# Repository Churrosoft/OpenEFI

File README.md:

# OpenEFI: 

OpenEFI es un sistema de inyección OpenSource configurable y adaptable a casi cualquier vehiculo con motores a Nafta/Gasohol/GNC/GLP

Está planeado el soporte a corto y largo plazo para:
-   Motores a nafta con inyección y encendido electrónico
-  calculo de tiempo de inyección a partir de tablas pre-definidas | Alpha Plus | Speed Density
-  Soporte de inyectores de alta impedancia (los de baja más adelante por requerir PWM además del tiempo de inyeccion)
-   Soporte para GNC/GLP con tablas independientes
-   Motores diesel con inyección directa
-   Motores de 1 a 8 cilindros

## Sobre el Software
la plataforma se ejecuta desde un STM32F103, conocido como "bluepill", para facilitar la programación del mismo, se utiliza el bootloader: [dapboot](https://github.com/devanlai/dapboot)

### Como generar los binarios:
se necesitan las siguientes herramientas:

    GNU Arm Embedded Toolchain
    sudo dnf install gcc systemd-devel ncurses-devel ncurses-compat-libs
    rustup override set nightly
    rustup target add thumbv7em-none-eabihf
    rustup component add llvm-tools-preview arm-none-eabi-newlib
    cargo install cargo-binutils cargo-embed cargo-flash cargo-expand

pasos para grabar el firmware:

 1. Compile y grabe el bootloader => [dapboot](https://github.com/devanlai/dapboot)
 2. clone el repositorio con git o descarguelo
 3. dentro del repo ejecutar: `make flash-usb`

## Sobre el Hardware

### Preguntas frecuentes:
### ¿hay algún video sobre el funcionamiento de la ECU / EFI ?
No, por el momento solo tenemos avances en el diseño de los pcb's, pero todavía el hardware ni el software se encuentra preparado para una prueba real en un motor, estimamos nuestro primer test a finales del 2020 si es que no nos morimos antes
### ¿cómo hacen para adaptar el hardware a una configuración tan amplia?
Porque el tratamiento de las señales analógicas para la mayoría de los sensores son iguales, consta de un filtro paso bajo y un diodo para evitar el sobre voltaje, se intentan mantener simples para que sea fácil de mantener, luego se aplican otros filtros en software para mejorar aún más esto

### ¿se pueden revisar los esquemas en algún lado, y obtener más información en general de la placa?
Claro!, todo lo referido al hardware se encuentra en [OpenEFI-PCB](https://github.com/openefi/OpenEFI-PCB)

## Sobre la configuracion

### Preguntas frecuentes:
### ¿como se va a configurar todo esto?
para la configuracion inicial, y para la visualizacion de parametros en tiempo real, se utiliza [OpenEFI-Tuner](https://github.com/openefi/OpenEFI-Tuner) , la idea es que tengas unicamente que conectar la EFI a tu computadora, entrar a [tuner.openefi.xyz](http://tuner.openefi.xyz/) y empezar a jugar, sin tener que pasar por la tortura de instalar drivers, programas,etc , aunque tambien puedes montar tu propio OpenEFI-Tuner en tu servidor local si quieres !, aunque la aplicación web funcionara sin conexión a internet

### ¿tiene soporte para un scanner común?¿cómo se leen los DTC's?
No, por el momento no tenemos planeado agregar soporte a CAN hasta llegar al MVP, así que no se pueden usar scanners automotrices normales acá
para leer los DTC se utiliza OpenEFI-Tuner

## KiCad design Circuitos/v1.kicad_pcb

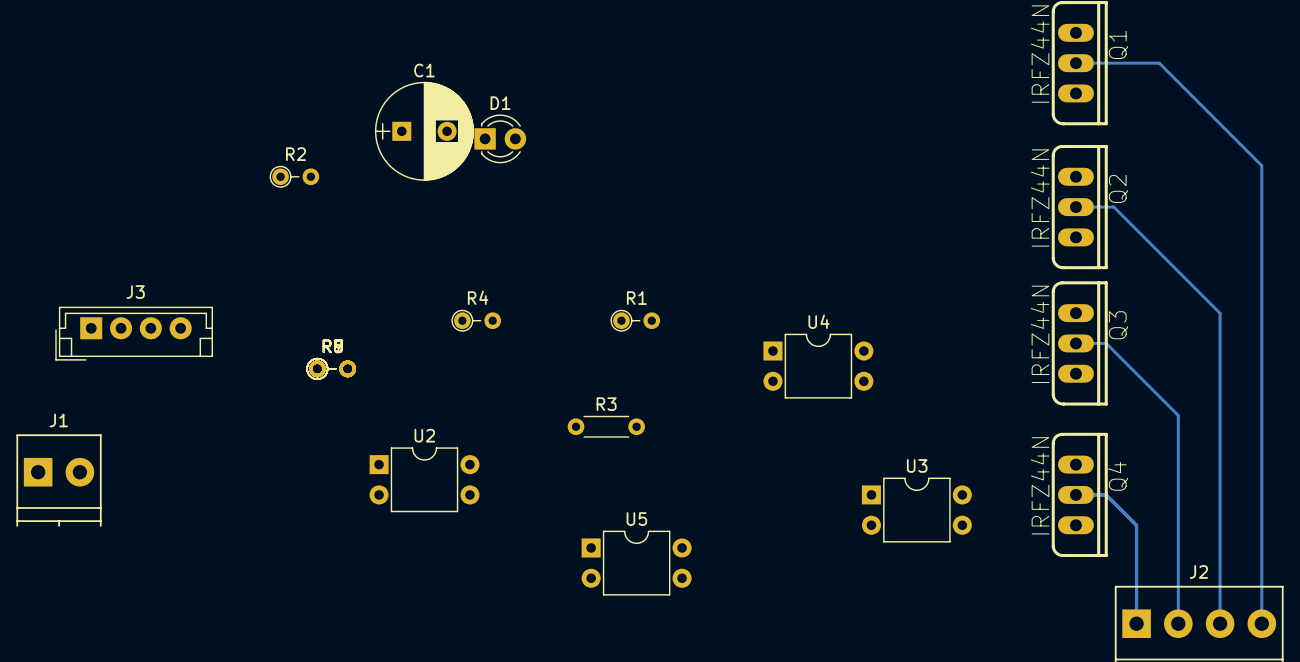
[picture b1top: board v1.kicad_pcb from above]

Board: 2 copper layers, 22 parts (0 on the bottom side), 19 nets.

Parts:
C1: 500u; CP_Radial_D8.0mm_P3.80mm
D1: LED; LED_D3.0mm_FlatTop
J1: 12v; TerminalBlock_Pheonix_PT-3.5mm_2pol
J2: Inyectores; TerminalBlock_Pheonix_PT-3.5mm_4pol
J3: CONN_01X04; JST_EH_B04B-EH-A_04x2.50mm_Straight
Q1, Q2, Q3, Q4: IRFZ44N; TO-220
R1: 1.2k; R_Axial_DIN0204_L3.6mm_D1.6mm_P2.54mm_Vertical
R2: 220r; R_Axial_DIN0204_L3.6mm_D1.6mm_P2.54mm_Vertical
R3: 4.7k; R_Axial_DIN0204_L3.6mm_D1.6mm_P5.08mm_Horizontal
R4, R6, R8: 220; R_Axial_DIN0204_L3.6mm_D1.6mm_P2.54mm_Vertical
R5: 4.7K; R_Axial_DIN0204_L3.6mm_D1.6mm_P2.54mm_Vertical
R7, R9: 4.7k; R_Axial_DIN0204_L3.6mm_D1.6mm_P2.54mm_Vertical
U2, U3, U4, U5: PC817; DIP-4_W7.62mm

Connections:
+12V: C1.1, J1.1, R1.1, R3.1, R5.1, R7.1, R9.1
Earth: C1.2, D1.1, J1.2, Q1.3, Q2.3, Q3.3, Q4.3, U2.2, U2.3, U3.2, U3.3, U4.2, U4.3, U5.2, U5.3
unnamed: D1.2, R1.2
unnamed: J2.1, Q4.2
unnamed: J2.2, Q3.2
unnamed: J2.3, Q2.2
unnamed: J2.4, Q1.2
unnamed: J3.1, R8.1
unnamed: J3.2, R6.1
unnamed: J3.3, R4.1
unnamed: J3.4, R2.2
unnamed: Q1.1, R3.2, U2.4
unnamed: Q2.1, R5.2, U3.4
unnamed: Q4.1, R9.2, U5.4
unnamed: R2.1, U2.1
unnamed: R4.2, U3.1
unnamed: R6.2, U4.1
unnamed: R7.2, U4.4
unnamed: R8.2, U5.1

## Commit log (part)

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2021-07-01 fix on launch_qemu script
2021-07-01 fix on core dump
2021-07-02 Create CNAME
2021-07-09 update on cpwm tests
2021-07-09 Deploy code docs to GitHub Pages build: 1016453644
    Commit: f49efb4e9a3f0d3858e90e6aa982c0b1a4395ed4
2021-07-12 added CPWM TIM3/4 stops
2021-08-03 FEAT: added tables namespace & basic operations
2021-08-23 Update on memory lib, now working simple I/O and DTC
2021-08-23 Updated deeps
2021-08-23 Deploy code docs to GitHub Pages build: 1157413025
    Commit: 3b184d702fc557cabea5c282cefa0d1845dd5d56
2021-08-23 Deploy code docs to GitHub Pages build: 1157451508
    Commit: c42740731e1a668fef26d181cf277c648f3431ef
2021-09-13 Deploy code docs to GitHub Pages build: 1231494850
    Commit: 5bd9b98b9723b0efd94b7c8af0e83e4001a633d5
2021-09-17 Deploy code docs to GitHub Pages build: 1244193873
    Commit: 0fabc0332efac8498607876999c042d3038082ba
2021-10-22 added ignition skeleton
2021-10-31 init pmic lib
2021-10-31 init webusb/control_interface code
2021-11-01 init webusb
2021-11-01 fix on process_frame / usb_cdc_if
2021-11-02 init tinyusb, not working
2021-11-02 full assert, change all char on cdc messages to uint8_t
2021-11-02 Deploy code docs to GitHub Pages build: 1413399338
    Commit: 7a87897e626b4160cce1ea6a59e9883043316fda
2021-11-04 added basic DTC check && common functions
2021-11-06 WIP: pmic dtc
2021-11-07 clean dtc functions
2021-11-07 added logs for injection/ignition registers
2021-11-09 minor fix on pmic
2021-11-09 SPI Working, 16Mhz clock, APB 8Mhz/16Mhz
2021-11-09 Deploy code docs to GitHub Pages build: 1441497642
    Commit: 279cf7ebe5776f444bb770d32a6d8fef5648664f
2021-11-10 32Mhz, 32-32 APB1
2021-11-15 wip: new memory lib
2021-11-18 clean main.cpp
2021-11-19 update deeps
2021-11-19 removed unused git dep
2021-11-19 bypass git commit erros on docs workflow
2021-11-20 Deploy code docs to GitHub Pages build: 1485550335
    Commit: 67af5ce9863826d8c5fd4a6f194a30d7fbc0cddf
2021-11-20 Deploy code docs to GitHub Pages build: 1485556337
    Commit: 969b88aafd36334eed82a1901a42424d64db6494
2021-11-20 Deploy code docs to GitHub Pages build: 1485568736
    Commit: df8b38b50a30b3eb1ae8ba0f820c8099bec0384a
2021-11-21 update on tables docs
2021-11-21 add tables to "Tables" module on doxygen
2021-11-21 fix addtogroup
2021-11-21 Deploy code docs to GitHub Pages build: 1486188713
    Commit: f7c0086929e30eba8c77736e418d7ed388bab34b
2021-11-27 Deploy code docs to GitHub Pages build: 1509794399
    Commit: 9b121dbe67fb439603781c0cc1f22537bcc6d86a
2021-12-03 Deploy code docs to GitHub Pages build: 1533751412
    Commit: b9104ecd271a490c1d45c628d70236e9f9446ee5
2021-12-24 Deploy code docs to GitHub Pages build: 1619996899
    Commit: 0f366000278b73afb32a38d6aa9cce0f127bae32
2021-12-24 Deploy code docs to GitHub Pages build: 1620003454
    Commit: e1af8d8e8f584061cc870fb3b91b4f4d0517b61b
2021-12-27 remove old usb files
2021-12-29 added webserial handler
2021-12-30 feat/webusb-tables, added basic table logic
2021-12-30 FEAT: WebSerial, read table from memory
2021-12-31 Deploy code docs to GitHub Pages build: 1639424144
    Commit: 4b64be70c5e0852dc5f9383cf8269caf9ffa4906
2022-01-04 Deploy code docs to GitHub Pages build: 1655948204
    Commit: 34130f2e801d7fce79e043f53d357108d9ee9b5f
2022-01-15 Deploy code docs to GitHub Pages build: 1700718618
    Commit: 53558dbc50a4f2d84345c06d540178410e54df73
2022-01-19 Deploy code docs to GitHub Pages build: 1716340558
    Commit: ee223321686fe4155cdb6493309cade1581cdb9e
2022-01-20 Deploy code docs to GitHub Pages build: 1720895698
    Commit: b3412914407d7c9e457cb63f76f27e256bfa9b82
2022-01-20 Deploy code docs to GitHub Pages build: 1721854263
    Commit: 43b6b9a9222052b53d707c965d56cabb615f6cdd
2022-01-23 Deploy code docs to GitHub Pages build: 1734966643
    Commit: 3ef56f0a33d6755fc373801c92773fc52597df15
2022-01-23 Deploy code docs to GitHub Pages build: 1735087944
    Commit: 9d922380e224e2591fbe0111e45802dc02b3d6a9
2022-01-24 Deploy code docs to GitHub Pages build: 1737586589
    Commit: 47d716514ab19abfa86c4fc6f8744ed08c57e846
2022-01-24 Deploy code docs to GitHub Pages build: 1742554132
    Commit: 755486aae8f00284daafb2e0aa637a1fab09f438
2022-01-24 bump sensors datasize from u16b to 32b
2022-01-25 fix webusb command crash
2022-01-31 fix MAP sensor *ponele*
2022-02-01 fix MAP::get_value
2022-02-03 Deploy code docs to GitHub Pages build: 1787734713
    Commit: 579d0b852aaadf1c419077d256d7fc0e3230d904
2022-02-05 Deploy code docs to GitHub Pages build: 1798473722
    Commit: da29d176e9ef3d0c08db56140d16a8405699ffbe
2022-02-20 updated sensors to MCP3208 adc, "it just works!"
2022-02-23 Deploy code docs to GitHub Pages build: 1885192609
    Commit: a0203b4a40d93ea7121798f93fac7c1cbd6f49df
2022-03-15 Deploy code docs to GitHub Pages build: 1989814801
    Commit: 51ca8f853e378f431f841141d17d8268b1103741
2022-03-29 Deploy code docs to GitHub Pages build: 2061678119
    Commit: 49189d71a0523734020142ddc3f9d7886315b779
2022-03-31 Deploy code docs to GitHub Pages build: 2073986722
    Commit: 3233be1ace1a9ae52a400febe78c226a04d7c764
2022-04-04 Deploy code docs to GitHub Pages build: 2087326653
    Commit: 0f93b00aa9f5c8ca35611cf387d53db2153d8b27
2022-04-11 new rpm calc
2022-04-12 updated tim1 source, added tim11 for rpm
2022-04-13 update HAL_TIM_PeriodElapsedCallback
2022-04-20 update hal internals
2022-04-28 bump core to uefi rev3
2022-04-28 remove adc
2022-05-07 wip v3
2022-05-12 updated core
2022-05-12 Deploy code docs to GitHub Pages build: 2311276295
    Commit: a6de2b014bd950bc46fe00f7edc9891d851b5039
2022-05-14 fix rpmdiff if
2022-05-16 cpwm: fix rpm calculation
2022-05-23 update C_PWM defines
2022-05-29 fix mockRPM
2022-05-29 added rpm status
2022-06-23 update webusb command definition
2022-06-28 "Funca o segfault", enviar trace por webserial
2022-06-30 fix webserial deque
2022-06-30 fix efi_invert_pin
2022-06-30 fix junit report message generation
2022-06-30 Deploy code docs to GitHub Pages build: 2592961736
    Commit: 1c75aba06defbba6776105cc38ca4eacd13c50e0
2022-07-01 CAN Wrapper headers
2022-07-06 add obd pid/status
2022-07-07 update NVIC priority
2022-07-29 add RPM::watch_dog
2022-08-17 can/obd wrapper init
2022-08-19 add can rx logic
2022-08-26 pa que recarajo pones el swap si luego vas a asignarlo como puntero lrpm
2022-08-27 fix OBD2 REQUEST_AVAILABLE_SID
2022-08-30 los swap ameooo, add CF logic to TX code
2022-09-05 Deploy code docs to GitHub Pages build: 2990528308
    Commit: 80d9df85cb7a8d346e4033e6bc3eaa170ef2f689
2022-09-06 Deploy code docs to GitHub Pages build: 2997390508
    Commit: b1b04253f7411039b74acb19d388a9bf06b12a13
2022-09-06 Deploy code docs to GitHub Pages build: 2997430793
    Commit: f43355f2547e79776dd6e6161ff541aad6274a79
2022-09-13 Deploy code docs to GitHub Pages build: 3042237243
    Commit: e7b73391949561e59798c9ae1bc705e1ac280b73
2022-09-13 Deploy code docs to GitHub Pages build: 3042253908
    Commit: f23cb249f4f15cab6e6a3582a7675c296464c21a
2022-09-16 Deploy code docs to GitHub Pages build: 3064888050
    Commit: f97e93bec8afc55a67206df36248d87ea51440e7
2022-09-27 Create LICENSE
2022-10-01 add .venv to gitignore
2022-10-04 fix sensors build
2022-10-06 Deploy code docs to GitHub Pages build: 3194318525
    Commit: db250aa3ef30542540a1e8f96d7bd9a610fb27f7
2022-10-06 Feature WebSerial: Add sensors/ignition/injection to core_status
2022-10-13 Deploy code docs to GitHub Pages build: 3245793454
    Commit: af0a6e2f804cc41290d5549539740356056c3188
2022-10-18 fix crc calculation, fix table read/write with offset
2022-10-19 update sensors lib
2022-10-21 Add CRC32 check on table write from Tuner (only full data, individual row wip)
2022-10-22 add mocks on webusb
2022-11-27 doxygen memory/tables
2022-12-03 wip injection, alpha N
2022-12-03 Deploy code docs to GitHub Pages build: 3610153926
    Commit: 2de543c3618dfd6996af6f8ea946c04486382581
2022-12-08 Deploy code docs to GitHub Pages build: 3644989836
    Commit: 0f0e014570b0edeb57b3a2ec89f83f73a9dbadf0
2022-12-13 WIP: injection timming, air model based on alphaN
2022-12-16 WIP: platformio testing
2022-12-20 wip alphaN tests
2022-12-22 fix lambda values, fix alphaN air calculation
2022-12-25 new config struct with memory backup
2022-12-26 fix efi_cfg
2022-12-31 fix table ram update
2023-01-08 add json lib
2023-01-08 fix firmware test build
2023-01-10 Deploy code docs to GitHub Pages build: 3886154374
    Commit: 34fbefca446bb27125b7482cc9a9118c8aa05cd1
2023-02-04 bootloader fix
2023-02-05 Ignore dirty w25qxx submodule
2023-02-05 Bootloader integration
2023-02-05 Deploy code docs to GitHub Pages build: 4098374462
    Commit: 687b344cd22707f27602d007917e0bf0b307f107
2023-02-05 Deploy code docs to GitHub Pages build: 4098441500
    Commit: 02182db54ea026f7fdd7927fdb9698a09ef84702
2023-02-09 add upload script
2023-02-09 wip core:gpio config
2023-02-09 Change target to thumbv7em-none-eabihf
2023-02-09 Add gdbinit for debugging within clion
2023-02-10 Improving debugging with clion
2023-02-10 wip gpio
2023-02-11 oneshot test
2023-02-11 soy un tarado.rs
2023-02-12 Move all modules into the app module.
2023-02-12 ckp trigger interrupt
2023-02-12 Sending CDC replies via task
2023-02-12 Log timestamps
2023-02-15 memory table read, wip validate from crc
2023-02-17 wip, fix memory erase
2023-02-24 fixes on calculate_injection_fuel
2023-02-27 fix gdb, wip json config
2023-03-12 wip: add cpwm && rpm control
2023-03-29 gpio rewrite
2023-04-01 no ser tan culiadazo para manejar los locks
2023-04-01 add table read over webserial
2023-04-17 injection/ignition demo
2023-04-21 add debug on ecn/iny/rly pins
2023-04-26 wip: ADC/Sensors code
2023-04-28 add spi proxy
2023-05-06 wip pmic module
2023-05-08 WIP: (needs docker image), add doc workflow
2023-05-08 Deploy code docs to GitHub Pages build: 4920617886
    Commit: 08f61bb1279d52ab45ec149a6354e51640b00632
2023-05-09 update repo url
2023-05-09 fix tag creation
2023-05-09 fix mas catolico para el tag v2
2023-05-13 FEAT: GH-76 add basic pmic commands
2023-05-15 FEAT: GH-76 (WIP) webserial interface
2023-05-26 add debug trace
2023-05-29 update clion cfg
2023-06-08 Deploy code docs to GitHub Pages build: 5216237670
    Commit: 781cde81ccea041bd0114002eed269018f476b38
2023-06-12 fix table data corruption on upload
2023-06-15 add ignition table
2023-06-15 re-add README.md
2023-06-15 Deploy code docs to GitHub Pages build: 5282945212
    Commit: 56db2f5b0f1b06b05d79d865396fbf7c43303d03
2023-06-18 Deploy code docs to GitHub Pages build: 5301337459
    Commit: f2b59a447f42e2be50ad8924ded11e79140c973b
2023-06-19 Deploy code docs to GitHub Pages build: 5314927451
    Commit: ca7011f596f05092d179f01fe36bc683c763e1ed
2023-06-22 Deploy code docs to GitHub Pages build: 5340890198
    Commit: bf96c17839af614c4a3b5c5294cbcfdbc674ee76
2023-06-22 update devcontainer
2023-06-24 add zsh
2023-06-24 Deploy code docs to GitHub Pages build: 5366134432
    Commit: 9899e8feeed3fcbbbeae15d8e7bb9ecaff7cf8f6
2023-06-27 Deploy code docs to GitHub Pages build: 5384496337
    Commit: 1adedf43149d542226c2efcc9cc4dc3322c2276d
2023-07-02 Deploy code docs to GitHub Pages build: 5434568000
    Commit: 49118c93e2bff7bcc3e8995b77ad8f7018c29c62
2023-07-11 Deploy code docs to GitHub Pages build: 5514322253
    Commit: 8f3cd71a303e734f04ffb180514d3c18b00518a1
2023-08-09 Deploy code docs to GitHub Pages build: 5803829801
    Commit: a385ea91d9c8033092d4df99949783af42714041
2023-08-13 Deploy code docs to GitHub Pages build: 5845549400
    Commit: b0f08d9a7d870d0dda417a2ca24b95678d13b9fc
2023-08-18 Deploy code docs to GitHub Pages build: 5897756588
    Commit: c7a3e14412b3e97d5f93391f731a61dd3dc07027
2023-08-25 Deploy code docs to GitHub Pages build: 5971833072
    Commit: c1c817b033fd277e098e1807f03af24f97ea1ed5
2023-09-03 add mononic timer, add stall control func
2023-09-13 init migration, added gpio
2023-09-14 add usb/webserial to main.rs
2023-09-16 wip webserial on rtic v2
2023-09-27 wip arch migration
2023-10-01 migrate pmic_cdc_callback
2023-10-04 migrate engine/cpwm tasks
2023-10-06 update ignition task, added watchdog
2023-11-24 Deploy code docs to GitHub Pages build: 6981426162
    Commit: 56151b8c78713a165b42d2c7625c8af45cf68c32
2023-11-27 added priority to SW tasks
